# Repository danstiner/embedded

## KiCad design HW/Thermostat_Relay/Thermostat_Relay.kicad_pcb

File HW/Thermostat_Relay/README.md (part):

# Thermostat relay board

## 1. Scope

Control board for two 24 VAC HVAC relays that can be driven by ESP32 GPIO pins. Compatible with
any single-stage gas furnace. Heat pumps are out of scope, they require additional relay channels.
Powering the ESP32 is also out of scope.

## 2. Background

Furnaces take mains power and step it down to 24 VAC. This is supplied on the R wire to a thermostat,
which can close the circuit with the W return wire to call for heat. In a modern furnace this is an
input to a digital control board and only draws a few milliamps. In older furnaces this directly
drives a relay coil and can draw an ampere or more of current.

## 3. Requirements

| ID   | Requirement                                                                                 |
| ---- | ------------------------------------------------------------------------------------------- |
| R-1  | Switch two independent circuits, R–W and R–G, each from one 3.3 V GPIO; high = closed       |
| R-2  | A circuit is open when its input is low or floating, or the MCU is off, in reset or booting |
| R-3  | Carry 1 A RMS continuously per circuit at 50 °C, and switch loads as small as 1 mA          |
| R-4  | Withstand 45 V peak (Class 2 transformer limit: 30 V RMS open-circuit, 42.4 V peak)         |
| R-5  | Survive switching off a 1 A inductive load                                                  |
| R-6  | Leak less than 100 µA through an open circuit                                               |
| R-7  | Galvanically isolate the MCU from the 24 VAC side                                           |
| R-8  | Draw no more than 10 mA per closed circuit from the MCU                                     |
| R-9  | Interrupt a short on the field wiring without damage to the wiring                          |
| R-10 | Surface-mount parts that can be reflowed on a hot plate; through-hole connectors            |

Notes
- 1 A is the load current TI's 24 VAC thermostat relay reference design (TIDA-010085) is
  specified for, and more than half of what a 40 VA Class 2 transformer can supply (1.7 A)
- 50 °C is a conservative ambient
- 30 V RMS maximum for thermostat circuits follows from them being Class 2 under UL 5085-3

## 4. Design trades

### 4.1 24 VAC switch

|                          | Relay    | **PhotoMOS** | Driver + FETs | TPSI8830    | TRIAC       |
| ------------------------ | -------- | ------------ | ------------- | ----------- | ----------- |
| Hold current (R-8)       | 70–90 mA | 5–10 mA      | ~5 mA         | ~5 mA       | ~10 mA      |
| 1 mA load (R-3)          | marginal | ✓            | ✓             | ✓           | ✗           |
| Leakage (R-6)            | ✓        | ✓            | ✓             | ✓           | ✗ (snubber) |
| Parts per channel        | 4        | 4            | ~10           | 3–4         | 5+          |
| Available to buy         | ✓        | ✓            | ✓             | ✗ (preview) | ✓           |
| Short-circuit protection | rugged   | none         | possible      | built in    | none        |

**Chosen: PhotoMOS.** An LED inside the package lights a photovoltaic cell that turns on two
back-to-back MOSFETs. It meets every requirement with only four parts per channel, making it easy
to use for bringing up a v1 board. A separate fuse is added for short-circuit protection.
Downsides of PhotoMOS are slightly higher cost and LED aging.

TI's reference designs for 24 VAC thermostat switching (section 10) both use discrete MOSFET pairs
with a separate isolated gate drive. This is likely a lower cost design at scale production,
using either small transformers or capacitive isolation instead of optocouplers. It also enables
microsecond switching for power-stealing, adding current-sensing circuitry, and the ability
to share one isolated supply across all channels. None of these are relevant to a v1 prototype.

TI's upcoming TPSI8830 is worth watching: it integrates a capacitively isolated driver with
back-to-back MOSFETs and overcurrent protection into a single package with 30 mΩ on resistance.

## 5. Circuit

Two identical channels share the R input, each with its own fuse. Only one channel is shown.

```
 logic side (3.3 V, USB ground) :        furnace side (24 VAC, floating)
                                :
 W_EN    o--+--[R1 220Ω]---+    :    +------+---[F1 2A]--- o R
            |            1 | U1 :    | 6    |
         [R2 10k]        [LED]~~:~~[FETs]  [D1 TVS]
            |            2 |    :    | 4    |
 GND     o--+--------------+    :    +------+------------- o W
```

### 5.1 Switch: Toshiba TLP3109A (U1)

| Datasheet value                 |                               | Requirement     |
| ------------------------------- | ----------------------------- | --------------- |
| Off-state voltage               | 100 V max                     | 45 V peak (R-4) |
| On-state current, AC connection | 3 A at 25 °C, 2.25 A at 50 °C | 1 A (R-3)       |
| On-resistance                   | 50 mΩ typ, 65 mΩ max          | –               |
| LED trigger current             | 3 mA max                      | see 5.2         |
| Off-state leakage, capacitance  | 1 µA max, 460 pF              | see 5.7         |
| Isolation                       | 1500 V RMS                    | galvanic (R-7)  |
| Pulse current                   | 9 A for 100 ms                | see 5.6         |

- Pins 4 and 6 (the two drains) are the switch; pin 5 (common source) is left open. That
  puts the two MOSFETs in series back to back, which is what lets the part block and
  conduct both polarities of AC.
- Heat: at 1 A and the maximum 65 mΩ the switch generates about 0.07 W of heat
- 100 V off-state max was chosen to have margin to clamp surges over the expected 42.4 V peak
  Class 2 transformer output, similar to TI reference design TIDA-010085.

Parts considered (DigiKey, 2026-11-12, quantity 1):

| Part         | Rating       | At 50 °C | R_on max | Isolation | Price           | Outcome     |
| ------------ | ------------ | -------- | -------- | --------- | --------------- | ----------- |
| **TLP3109A** | 100 V, 3 A   | 2.25 A   | 65 mΩ    | 1500 V    | $4.14, in stock | chosen      |
| TLP3546A     | 100 V, 3.5 A | 2.6 A    | 80 mΩ    | 2500 V    | $4.11, no stock | unavailable |

### 5.2 LED resistor: 220 Ω (R1)

The TLP3109A datasheet recommends 5 to 25 mA. `I = (V_GPIO − V_LED) / R`:

| Case            | V_GPIO | V_LED  | I      |
| --------------- | ------ | ------ | ------ |
| Worst-case low  | 3.0 V  | 1.80 V | 5.4 mA |
| Nominal         | 3.3 V  | 1.65 V | 7.5 mA |
| Worst-case high | 3.47 V | 1.50 V | 9.0 mA |

### 5.3 Optional pull-down: 10 kΩ (R2)

Optional pull-down to hold the LED input at ~0 V when not being driven (R-2). Overrides the
pull-up glitch during boot that some ESP32 pins exhibit. Optional because the TLP3109A is
guaranteed off below 0.1 mA of LED current, and a 45 kΩ pull-up supplies only about 0.05 mA.
Cannot override a pin that actively drives high during boot, those high-level glitch pins
should be avoided.

### 5.4 Optional indicator: 4.7 kΩ and a red LED

One LED per channel, from the control input to ground, lit while the ESP32 commands the
channel closed. At 4.7 kΩ it draws about 0.3 mA, 0.4 mA worst case. With the pull-down and
indicator both fitted, a closed channel draws at most 9.0 + 0.35 + 0.4 = 9.7 mA (R-8).

### 5.5 Clamp: Bidirectional TVS (D1)

When the switch opens on a relay coil or gas valve, the coil's inductance creates a voltage
spike across the switch. A bidirectional TVS across the switch limits that voltage (R-5)
to prevent damage to the switch.

|                     | SMBJ48CA       | Requirement                       |
| ------------------- | -------------- | --------------------------------- |
| Reverse stand off   | 48 V           | ≥ 45 V peak (R-4)                 |
| Max clamp           | 77.4 V @ 7.8 A | ≤ 80 V (switch's recommended max) |
| Max reverse leakage | 1 µA           | < 100 µA total leakage (R-6)      |

An RC snubber is ruled out by R-6: a typical 100 nF passes about 1.1 mA at 60 Hz with the
switch open, which could trigger a phantom call for heat on a modern furnace control board.

### 5.6 Fuses: 2 A very fast-acting, one per channel (F1, F2)

Each fuse opens if its W or G circuit is shorted while that channel is closed (R-9): a
shorted relay coil, or the wire touching the transformer's return or grounded metal. That
protects the cable, the transformer and, for moderate fault currents, the switch. One fuse
per channel means a fault on the fan wire cannot take out the heat, and each fuse is sized
for one load, not the sum.

| Littelfuse 0466002.NR | Datasheet                            | Requirement                                                         |
| --------------------- | ------------------------------------ | ------------------------------------------------------------------- |
| Voltage rating        | 63 VAC                               | 30 V RMS (R-4)                                                      |
| Interrupting rating   | 50 A at 63 VAC                       | transformer short-circuit current: unmeasured, estimated 10 to 20 A |
| Continuous current    | 1.5 A at 25 °C, about 1.3 A at 50 °C | 1 A (R-3)                                                           |
| Opens at 200 % (4 A)  | within 5 s                           | –                                                                   |
| Opens at 300 % (6 A)  | within 0.2 s                         | –                                                                   |
| Melting I²t           | 0.23 A²s                             | below the switch's 8 A²s                                            |
| Cold resistance       | 30 mΩ                                | –                                                                   |

- Sizing: Littelfuse's guidance is to run a fuse at no more than 75 % of its rating at
  25 °C, which gives 1.5 A. The datasheet rerates a further 20 % at 70 °C; interpolating,
  about 11 % at 50 °C gives 1.3 A. That leaves about 30 % margin over a 1 A load. Relay
  coil inrush against the low melting I²t is unverified (section 9).
- Compared with others: TI recommends the same 2 A fast fuse for its 1 A design
  (TIDA-010085) and tested with the 1.5 A part of this series. Furnace control boards
  commonly fuse the whole 24 V circuit at 3 or 5 A, so a 2 A fuse here should open first.
- Overloads: the fuse's 2 A rating is below the switch's 2.25 A rating at 50 °C. It holds
  2 A indefinitely and opens slowly just above that (4 A in 5 s and 6 A in 0.2 s are
  specified), so
  moderate overloads are covered loosely, not tightly.
- Shorts: the switch tolerates 9 A for 100 ms, about 8 A²s. At 9 A the fuse melts in
  roughly 3 ms (0.23 A²s / (9 A)²), so the switch should survive a short the transformer
  limits to 9 A. Above 9 A the switch is outside its rating however fast the fuse clears.
  For scale, TI measured about 7 A peak from a shorted 20 VA transformer in TIDA-010085.

Why not a resettable PTC:

|                                      | Fuse, 2 A (chosen) | PTC, e.g. 2920L110/60 (1.1 A hold) |
| ------------------------------------ | ------------------ | ---------------------------------- |
| Carries 1 A at 50 °C                 | yes                | no: hold current falls to 0.83 A   |
| Clears a 9 A short in                | about 3 ms         | about 0.5 s (at 8 A)               |
| Lets through (switch survives 8 A²s) | about 0.2 A²s      | tens of A²s                        |
| After a fault                        | replace the part   | resets itself                      |

A PTC large enough to carry 1 A hot trips more slowly still, so it would protect the
wiring but not the switch. A fuse drawn as a thin PCB trace is not an option: it has no
defined rating and fails by burning the board.

### 5.7 Leakage when open (R-6)

At 30 VAC, 60 Hz: 1 µA (switch) + 5.2 µA (its 460 pF) + 1 µA (TVS) + about 6 µA (TVS
capacitance, about 500 pF read off the datasheet graph) ≈ 13 µA, against a 100 µA limit.

### 5.8 Isolation (R-7)

Isolation is needed because the two sides have unrelated references. The furnace's 24 VAC
secondary is often bonded to chassis earth at C, and the ESP32's USB ground can reach earth
through a PC or charger; a shared connection would tie the two together, and R, W and G
swing up to ±42 V against it, far outside what a GPIO tolerates. A switch for AC also has
to float with the line it switches.

The only link between the two sides is the light path inside U1 and U2, rated 1500 V RMS.
That is far above anything a 24 VAC Class 2 circuit produces, but it is functional
isolation, not a safety rating. The field side is never connected to logic ground; C is a
parking terminal.

### 5.9 PCB layout

| Rule                                 | Value     | Basis                                                        |
| ------------------------------------ | --------- | ------------------------------------------------------------ |
| Field trace width, 1 oz outer layer  | ≥ 0.93 mm | IPC-2152: 10 °C rise at 2 A (fuse rating)                    |
| Spacing between different field nets | ≥ 0.64 mm | IPC-2221C Table 6-1, 51–100 V, bare external conductors (B2) |
| Logic copper to field copper         | ≥ 4.0 mm  | creepage of the 2.54SOP package; no copper under U1 and U2   |

- Trace width: the minimum comes from the Brooks and Adam fit to the IPC-2152 data that
  KiCad's calculator uses, ΔT = 215.3 · I² · W^−1.15 · Th^−1 (W and Th in mils), for a 10
  °C rise at 2 A in 35 µm copper. The older IPC-2221 formula gives 0.78 mm for the same
  conditions. The board uses copper pours at least 1.4 mm wide for the switched nets on
  the front, a pour on the back for R, and 1.0 mm traces with two vias from each fuse to
  that pour. A short does not matter here: the fuse melts in milliseconds.
- Field spacing: the working voltage is at most 42.4 V peak (R-4), but the clamp lets a
  turn-off transient reach 77 V (5.5), so the 51–100 V row applies. It asks for 0.64 mm
  between bare conductors, 0.5 mm between uncoated component leads and 0.3 mm under solder
  mask. Using 0.64 mm everywhere covers all three.
- Logic to field: no standard sets a distance for functional isolation of a Class 2
  circuit, so the relay package is the limit. The TLP3109A datasheet does not state its
  creepage; Toshiba's 2014 photocoupler catalog lists 4.0 mm minimum creepage and
  clearance for the 2.54SOP4/6/8 package family. The footprint's input and output pads are
  5.1 mm apart, and the layout keeps at least 4.9 mm between all logic and field copper,
  including the ground pours on both layers of the logic side.

## 6. Bill of materials

| Ref    | Value              | Part               | Footprint   | Description                                   |
| ------ | ------------------ | ------------------ | ----------- | --------------------------------------------- |
| U1, U2 | TLP3109A           | Toshiba            | 2.54SOP6    | PhotoMOS relay, 100 V, 1 A at 50 °C (5.1)     |
| R1, R3 | 220 Ω, 1 %         | any                | 0603        | RES - Input current limit (5.2)               |
| R2, R4 | 10 kΩ              | any                | 0603        | Input pull-down, optional (5.3)               |
| D1, D2 | 48 V               | SMBJ48CA           | SMB         | Bidirectional TVS, 48 V standoff (5.5)        |
| F1, F2 | 2 A very fast      | Littelfuse 0466002 | 1206        | Fuse, ≥ 30 VAC, ≥ 20 A interrupting (5.6)     |
| R5, R6 | 4.7 kΩ             | any                | 0603        | RES - Indicator current limit, optional (5.4) |
| D3, D4 | Red LED            | any                | 0603        | LED, Red, SMD - Indicator, optional (5.4)     |
| J1     | 1×3 pin header     | any                | 2.54 mm THT | MCU Connection                                |
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
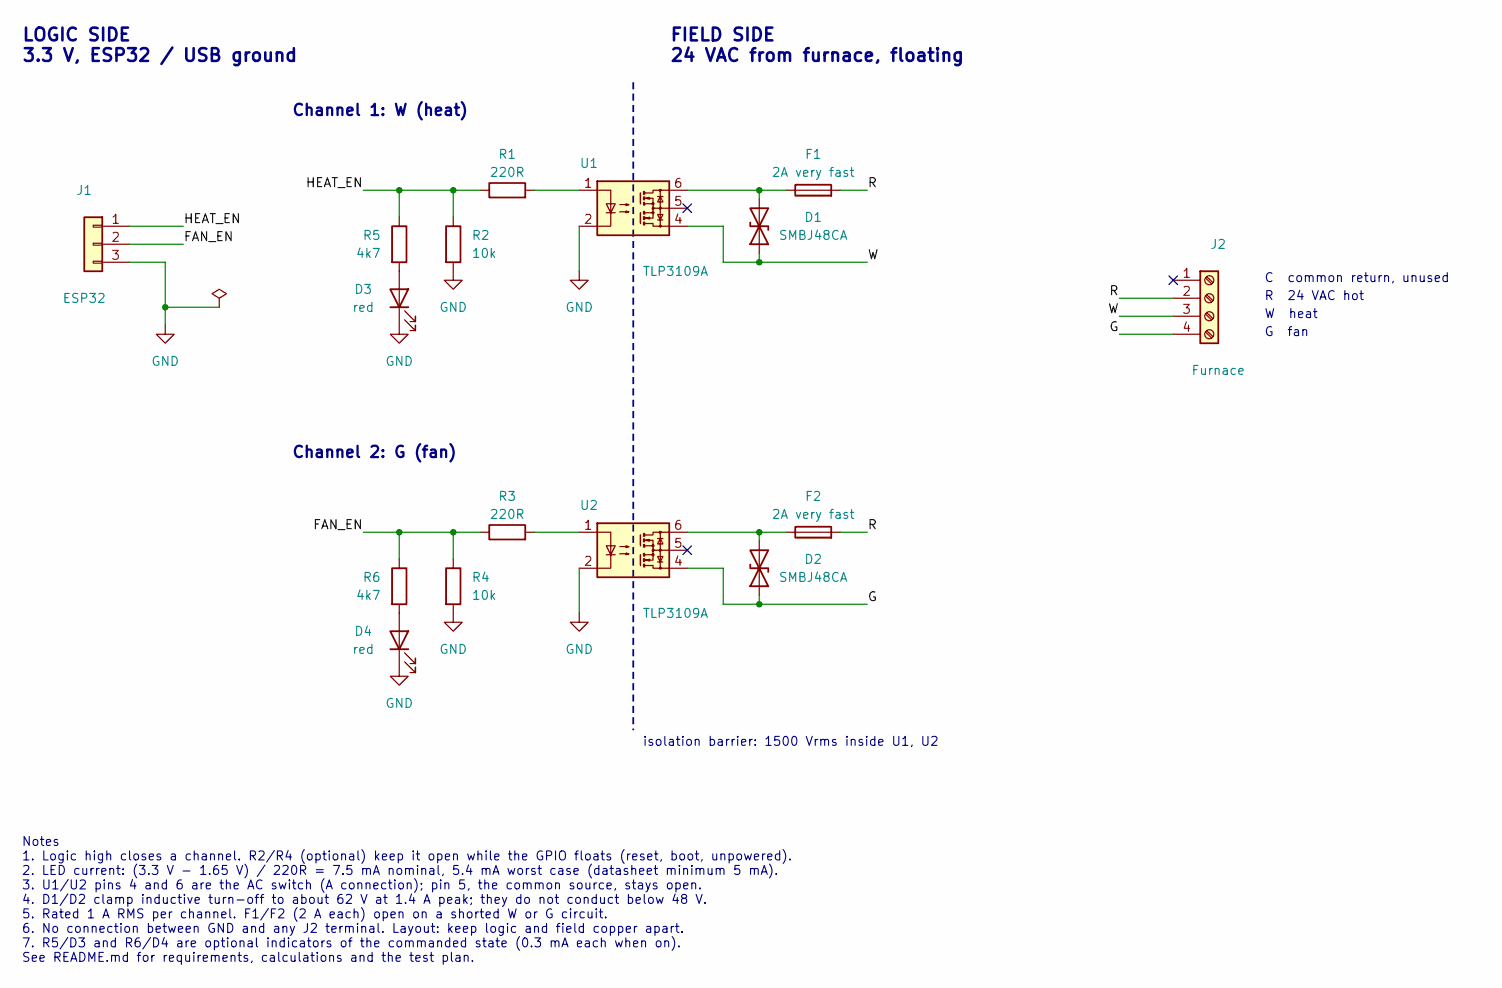
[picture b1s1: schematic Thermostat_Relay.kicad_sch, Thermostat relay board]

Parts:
D1, D2: SMBJ48CA; D_SMB_Handsoldering; MPN SMBJ48CA
D3, D4: red; LED_0603_1608Metric_Pad1.05x0.95mm_HandSolder; MPN 150060SS75000
F1, F2: 2A very fast; Fuse_1206_3216Metric_Pad1.42x1.75mm_HandSolder; MPN 0466002.NR
J1: ESP32; PinHeader_1x03_P2.54mm_Vertical
J2: Furnace; TerminalBlock_Phoenix_MKDS-1,5-4-5.08_1x04_P5.08mm_Horizont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
R1, R3: 220R; R_0603_1608Metric_Pad0.98x0.95mm_HandSolder; Tolerance 1%; MPN RC0603FR-07220RL
R2, R4: 10k; R_0603_1608Metric_Pad0.98x0.95mm_HandSolder; MPN RC0603FR-0710KL
R5, R6: 4k7; R_0603_1608Metric_Pad0.98x0.95mm_HandSolder; MPN RC0603FR-074K7L
U1, U2: TLP3109A; Toshiba_11-7C1S_2.54SOP6_4.4x6.3mm_P2.54mm; MPN TLP3109A(TP,F

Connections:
/G: D2.1 (A1), J2.4, U2.4
/G_EN: J1.2, R3.1, R4.1, R6.1
/R: F1.2, F2.2, J2.2
/W: D1.1 (A1), J2.3, U1.4
/W_EN: J1.1, R1.1, R2.1, R5.1
GND: D3.1 (K), D4.1 (K), J1.3, R2.2, R4.2, U1.2, U2.2
unnamed: D1.2 (A2), F1.1, U1.6
unnamed: D2.2 (A2), F2.1, U2.6
unnamed: D3.2 (A), R5.2
unnamed: D4.2 (A), R6.2
unnamed: R1.2, U1.1
unnamed: R3.2, U2.1

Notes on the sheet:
FIELD SIDE 24 VAC from furnace, floating
R 24 VAC hot
LOGIC SIDE 3.3 V, ESP32 / USB ground
Channel 2: G (fan)
W heat
Channel 1: W (heat)
Notes 1. Logic high closes a channel. R2/R4 (optional) keep it open while the GPIO floats (reset, boot, unpowered). 2. LED current: (3.3 V - 1.65 V) / 220R = 7.5 mA nominal, 5.4 mA worst case (datasheet minimum 5 mA). 3. U1/U2 pins 4 and 6 are the AC switch (A connection); pin 5, the common source,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
G fan
C common return, unused
isolation barrier: 1500 Vrms inside U1, U2

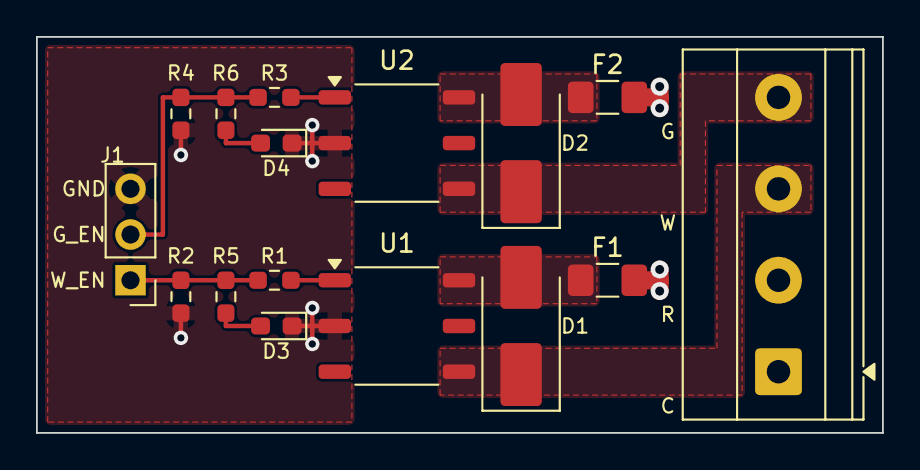
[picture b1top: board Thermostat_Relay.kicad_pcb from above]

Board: 2 copper layers, 47.0 x 22.0 mm, 16 parts (0 on the bottom side), 12 nets.

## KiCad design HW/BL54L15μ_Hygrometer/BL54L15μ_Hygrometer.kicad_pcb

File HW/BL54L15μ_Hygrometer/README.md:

+-----------+-----+----------------------+-----------------------------------------+--------------------------------------------------------------------------------------+
| Reference | Qty | Value                | Part Number                             | Footprint                                                                            |
+-----------+-----+----------------------+-----------------------------------------+--------------------------------------------------------------------------------------+
| BT1       | 1   | CR2 Battery          | 1011                                    | 1011:BAT_1011                                                                        |
| BZ1       | 1   | AST0827MW-03BTRQ     | AST0827MW-03BTRQ                        | AST0827MW-03BTRQ:AST0827MW-03BTRQ_MAL                                                |
| C1        | 1   | 100nF                | GRM155R61A104KA01J                      | Capacitor_SMD:C_0402_1005Metric                                                      |
| C2,C3     | 2   | 10μF                 | CL10A106KP8NNNC                         | Capacitor_SMD:C_0603_1608Metric                                                      |
| D1,D2     | 2   | 5V TVS               | TPD1E10B06DPYR                          | Diode_SMD:D_0402_1005Metric                                                          |
| D3        | 1   | MBR0520L             | MBR0520LT3G                             | Diode_SMD:D_SOD-123                                                                  |
| IC1       | 1   | nrf54L 453-00223R    | 453-00223R                              | 453-00223R:45300223R                                                                 |
| J1        | 1   | Conn_ARM_JTAG_SWD_10 | 3220-10-0300-00                         | Connector_PinHeader_1.27mm:PinHeader_2x05_P1.27mm_Vertical_SMD                       |
| P1,P2     | 2   | 6mmMetalDome         | Triangle 6mm - 0.8mm feet               | MetalDomeSwitch:TriangleDome_Diameter6mm                                             |
| Q1        | 1   | AOSS32136C           | AOSS32136C                              | Package_TO_SOT_SMD:SOT-23-3                                                          |
| R1,R2     | 2   | 10kΩ                 | RC0402FR-0710KL                         | Resistor_SMD:R_0402_1005Metric                                                       |
| R3,R7     | 2   | 1MΩ                  | RC0402FR-071ML                          | Resistor_SMD:R_0402_1005Metric                                                       |
| U1        | 1   | SHT4x                | SHT45-AD1F-R2                           | Sensor_Humidity:Sensirion_DFN-4_1.5x1.5mm_P0.8mm_SHT4x_NoCentralPad                  |
| X1        | 1   | 32.768 kHz           | CM7V-T1A-LOW-ESR-32.768KHZ-9PF-20-TA-QC | CM7V_T1A_LOW_ESR_32_768KHZ_9PF_20_TA_QC:XTAL_CM7V-T1A-LOW-ESR-32.768KHZ-9PF-20-TA-QC |
+-----------+-----+----------------------+-----------------------------------------+--------------------------------------------------------------------------------------+

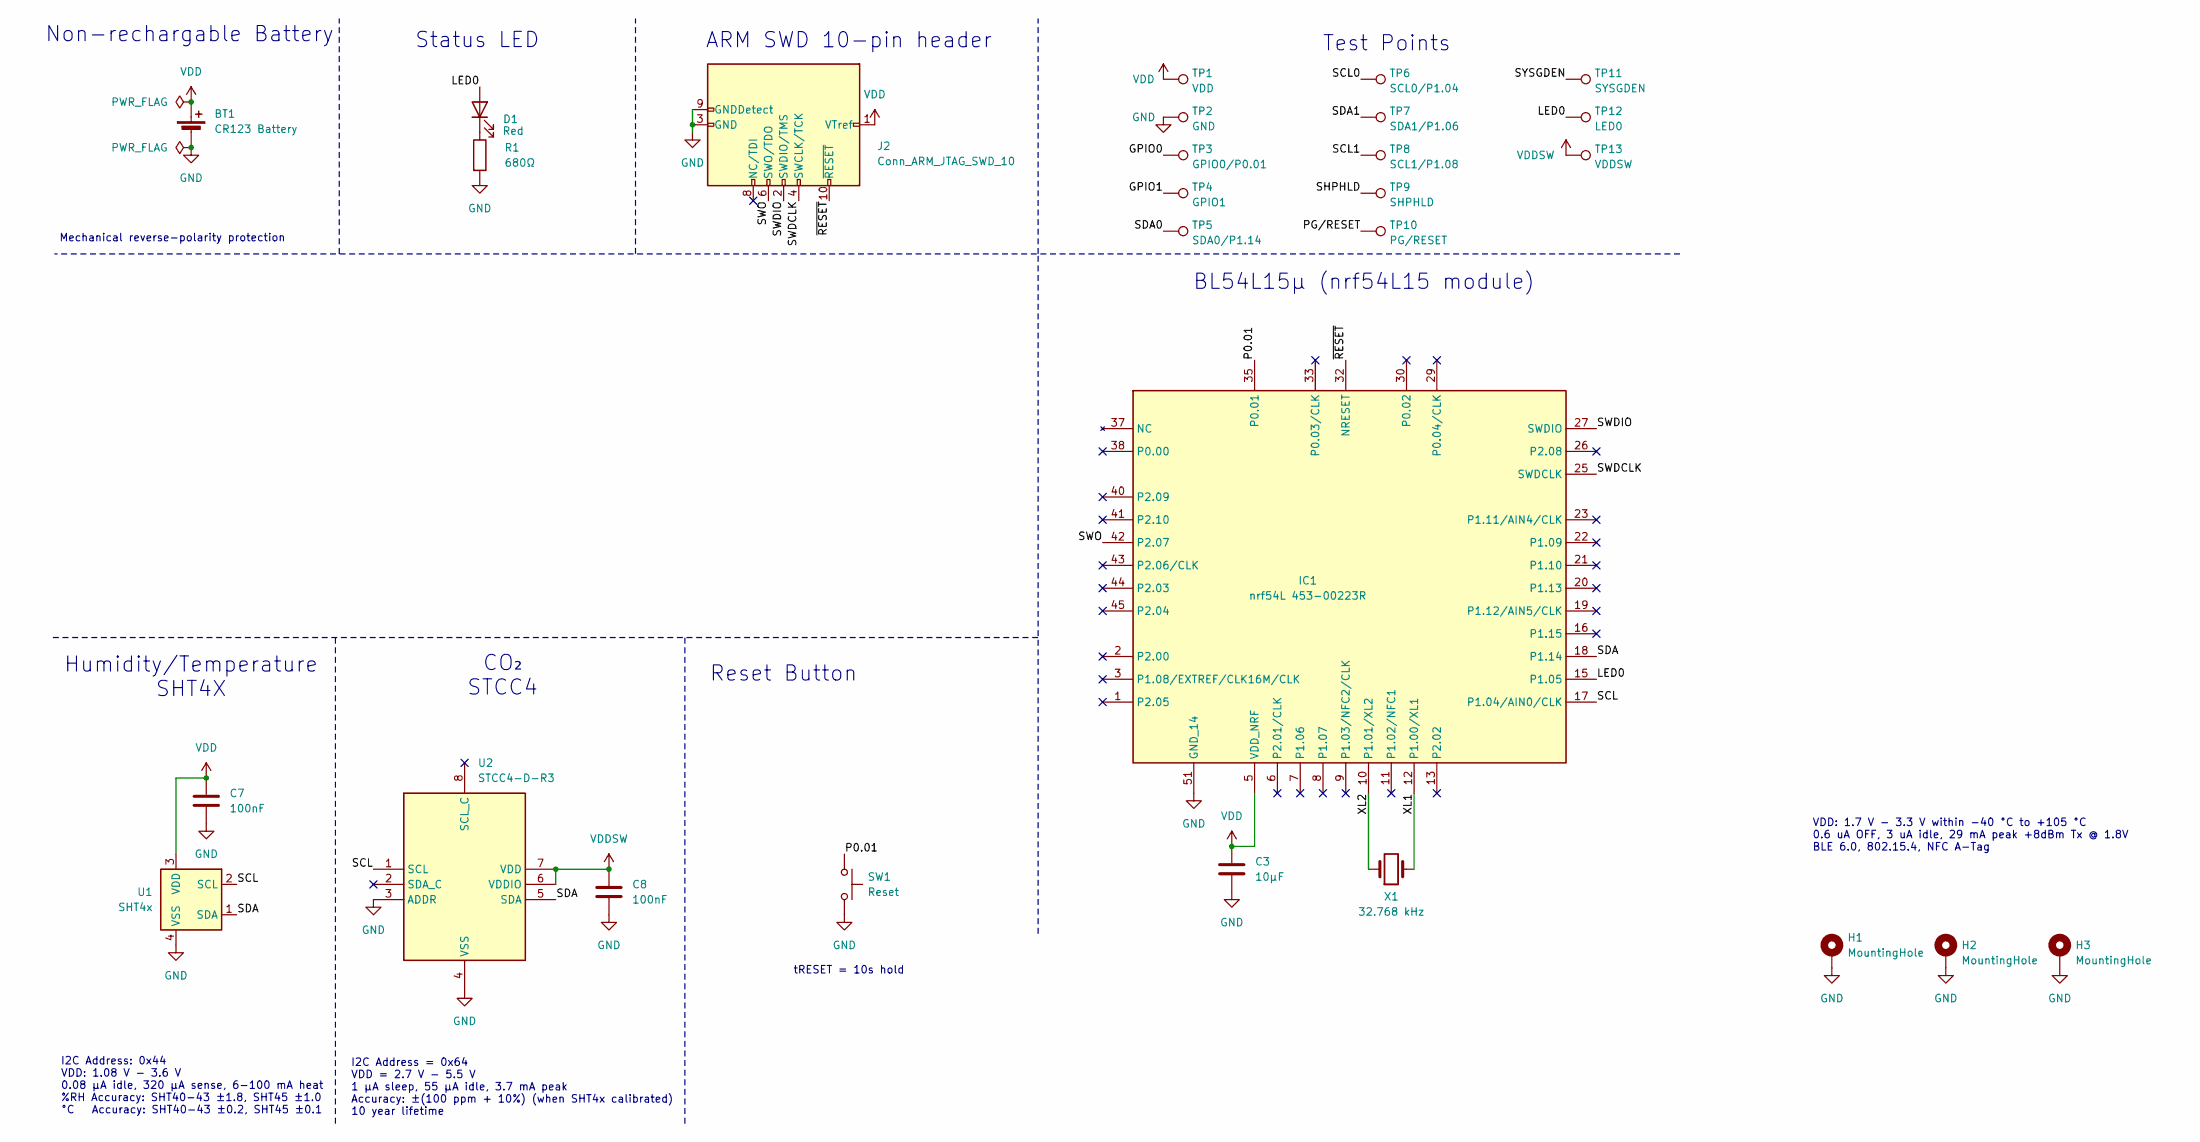
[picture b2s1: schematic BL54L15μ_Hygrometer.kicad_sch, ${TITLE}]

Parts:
BT1: CR123 Battery; BAT_1011; Part Number 1011
C3: 10μF; C_0603_1608Metric; Part Number CL10A106KP8NNNC
C7, C8: 100nF; C_0402_1005Metric; Part Number GRM155R61A104KA01J
D1: PWRLED; LED_0603_1608Metric; Part Number 150060SS75000; Digikey Part Number 732-4979-1-ND
H1, H2, H3: MountingHole; MountingHole_2.2mm_M2_Pad
IC1: nrf54L 453-00223R; 45300223R; Part Number 453-00223R; Digikey Part Number 776-453-00223RCT-ND
J2: Conn_ARM_JTAG_SWD_10; PinHeader_2x05_P1.27mm_Vertical_SMD; Digikey Part Number 1528-752-ND
R1: 680Ω; R_0603_1608Metric; Part Number RC0603JR-13680RL
SW1: Reset; SW_Push_SPST_NO_Alps_SKRK; Part Number SKRKAHE020; Digikey Part Number 4809-SKRKAHE020CT-ND
TP1: VDD; TestPoint_Pad_D1.0mm
TP2: GND; TestPoint_Pad_1.0x1.0mm
TP3: GPIO0/P0.01; TestPoint_Pad_D1.0mm
TP4: GPIO1; TestPoint_Pad_D1.0mm
TP5: SDA0/P1.14; TestPoint_Pad_D1.0mm
TP6: SCL0/P1.04; TestPoint_Pad_D1.0mm
TP7: SDA1/P1.06; TestPoint_Pad_D1.0mm
TP8: SCL1/P1.08; TestPoint_Pad_D1.0mm
TP9: SHPHLD; TestPoint_Pad_D1.0mm
TP10: PG/RESET; TestPoint_Pad_D1.0mm
TP11: SYSGDEN; TestPoint_Pad_D1.0mm
TP12: LED0; TestPoint_Pad_D1.0mm
TP13: VDDSW; TestPoint_Pad_D1.0mm
U1: SHT4x; Sensirion_DFN-4_1.5x1.5mm_P0.8mm_SHT4x_NoCentralPad; Part Number SHT45-AD1F-R2
U2: STCC4-D-R3; STCC4DR3; Part Number STCC4-D-R3; Digikey Part Number 1649-STCC4-D-R3CT-ND
X1: 32.768 kHz; XTAL_CM7V-T1A-LOW-ESR-32.768KHZ-9PF-20-TA-QC; Part Number CM7V-T1A-LOW-ESR-32.768KHZ-9PF-20-TA-QC; Digikey Part Number 2195-CM7VT1ALOWESR32.768KHZ9PF20TAQCCT-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

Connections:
/GPIO0: TP3.1 (1_1)
/GPIO1: TP4.1 (1_1)
/LED0: D1.2 (A), IC1.15 (P1.05), TP12.1 (1_1)
/P0.01: IC1.35 (P0.01), SW1.1
/PG/RESET: TP10.1 (1_1)
/SCL: IC1.17 (P1.04/AIN0/CLK), U1.2 (SCL), U2.1 (SCL)
/SCL0: TP6.1 (1_1)
/SCL1: TP8.1 (1_1)
/SDA: IC1.18 (P1.14), U1.1 (SDA), U2.5 (SDA)
/SDA0: TP5.1 (1_1)
/SDA1: TP7.1 (1_1)
/SHPHLD: TP9.1 (1_1)
/SWDCLK: IC1.25 (SWDCLK), J2.4 (SWCLK/TCK)
/SWDIO: IC1.27 (SWDIO), J2.2 (SWDIO/TMS)
/SWO: IC1.42 (P2.07), J2.6 (SWO/TDO)
/SYSGDEN: TP11.1 (1_1)
/XL1: IC1.12 (P1.00/XL1), X1.2
/XL2: IC1.10 (P1.01/XL2), X1.1
/~RESET: IC1.32 (NRESET), J2.10 (~RESET)
GND: BT1.2 (-), C3.2, C7.2, C8.2, H1.1 (1_1), H2.1 (1_1), H3.1 (1_1), IC1.4 (GND_1), IC1.14 (GND_2), IC1.24 (GND_3), IC1.28 (GND_4), IC1.31 (GND_5), IC1.34 (GND_6), IC1.36 (GND_7), IC1.39 (GND_8), IC1.46 (GND_9), IC1.47 (GND_10), IC1.48 (GND_11), IC1.49 (GND_12), IC1.50 (GND_13), IC1.51 (GND_14), J2.3 (GND), J2.5 (GND), J2.9 (GNDDetect), R1.2, SW1.2, TP2.1 (1_1), U1.4 (VSS), U2.3 (ADDR), U2.4 (VSS)
unnamed: D1.1 (K), R1.1
VDD: BT1.1 (+), C3.1, C7.1, IC1.5 (VDD_NRF), J2.1 (VTref), TP1.1 (1_1), U1.3 (VDD)
VDDSW: C8.1, TP13.1 (1_1), U2.6 (VDDIO), U2.7 (VDD)

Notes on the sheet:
Mechanical reverse-polarity protection
VDD: 1.7 V - 3.3 V within -40 °C to +105 °C 0.6 uA OFF, 3 uA idle, 29 mA peak +8dBm Tx @ 1.8V BLE 6.0, 802.15.4, NFC A-Tag
Humidity/Temperature SHT4X
CO₂ STCC4
tRESET = 10s hold
I2C Address = 0x64 VDD = 2.7 V - 5.5 V 1 μA sleep, 55 μA idle, 3.7 mA peak Accuracy: ±(100 ppm + 10%) (when SHT4x calibrated) 10 year lifetime
Test Points
Non-rechargable Battery
BL54L15μ (nrf54L15 module)
Status LED
I2C Address: 0x44 VDD: 1.08 V - 3.6 V 0.08 μA idle, 320 μA sense, 6-100 mA heat %RH Accuracy: SHT40-43 ±1.8, SHT45 ±1.0 °C Accuracy: SHT40-43 ±0.2, SHT45 ±0.1
ARM SWD 10-pin header
Reset Button

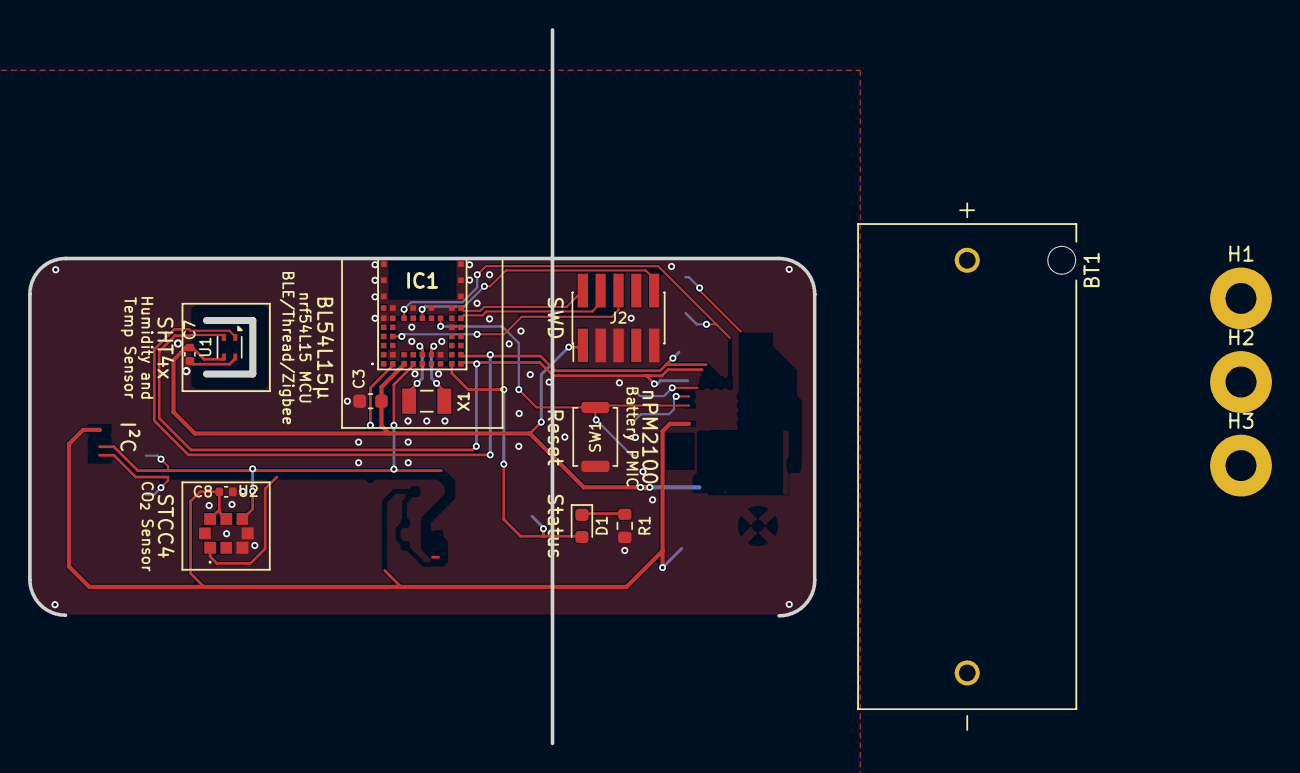
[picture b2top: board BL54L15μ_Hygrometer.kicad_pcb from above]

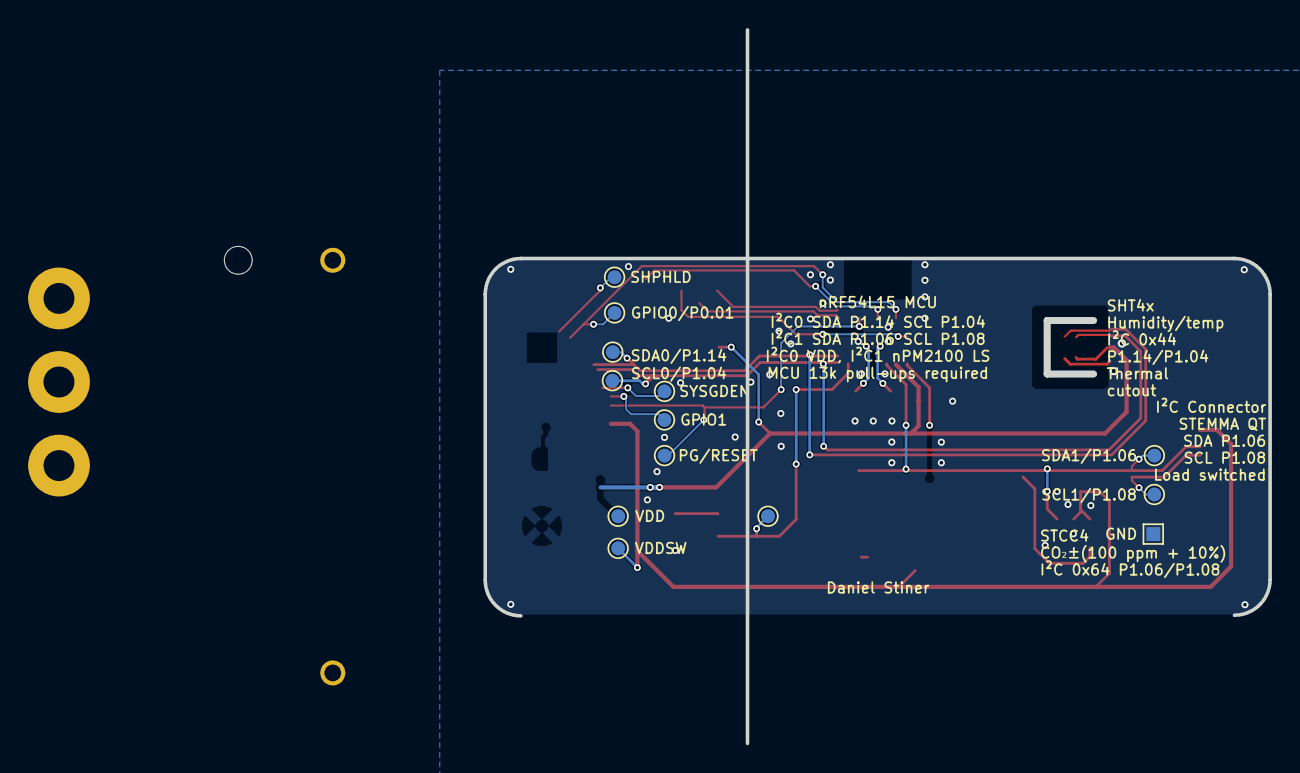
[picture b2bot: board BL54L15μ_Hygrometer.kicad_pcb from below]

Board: 2 copper layers, 55.9 x 50.8 mm, 28 parts (13 on the bottom side), 14 nets.

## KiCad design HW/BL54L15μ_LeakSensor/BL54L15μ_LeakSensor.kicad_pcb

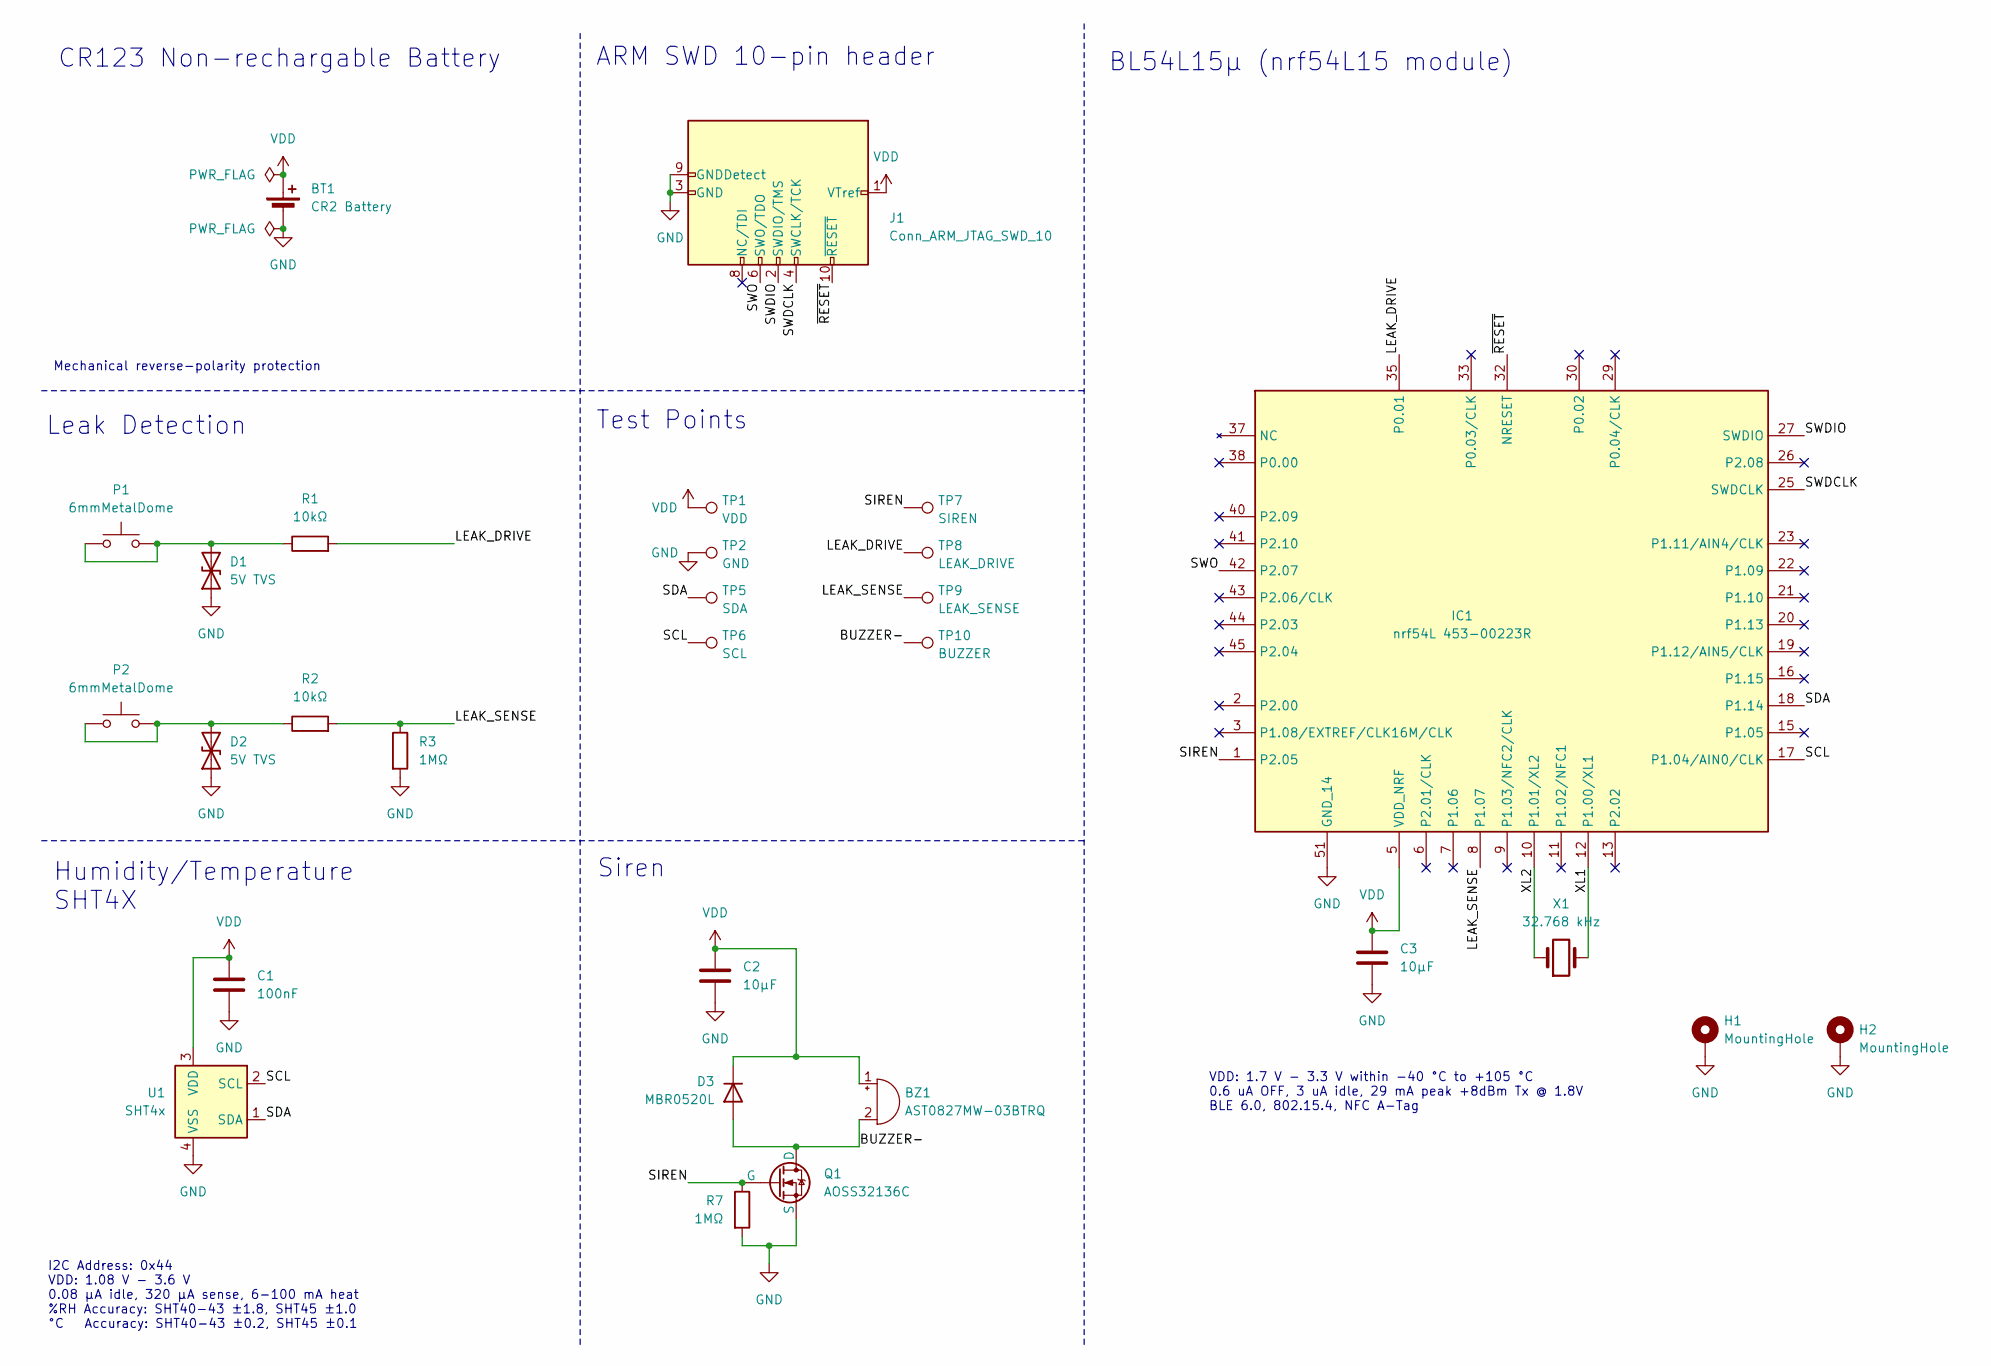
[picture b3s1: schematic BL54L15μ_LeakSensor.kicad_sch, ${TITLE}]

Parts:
BT1: CR2 Battery; BAT_1011; Part Number 1011
BZ1: AST0827MW-03BTRQ; AST0827MW-03BTRQ_MAL; Part Number AST0827MW-03BTRQ
C1: 100nF; C_0402_1005Metric; Part Number GRM155R61A104KA01J
C2, C3: 10μF; C_0603_1608Metric; Part Number CL10A106KP8NNNC
D1, D2: 5V TVS; D_0402_1005Metric; Part Number TPD1E10B06DPYR
D3: MBR0520L; D_SOD-123; Part Number MBR0520LT3G
H1, H2: MountingHole; MountingHole_2.2mm_M2_Pad
IC1: nrf54L 453-00223R; 45300223R; Part Number 453-00223R; Digikey Part Number 776-453-00223RCT-ND
J1: Conn_ARM_JTAG_SWD_10; PinHeader_2x05_P1.27mm_Vertical_SMD; Part Number 3220-10-0300-00
P1, P2: 6mmMetalDome; TriangleDome_Diameter6mm; Part Number Triangle 6mm - 0.8mm feet
Q1: AOSS32136C; SOT-23-3; Part Number AOSS32136C
R1, R2: 10kΩ; R_0402_1005Metric; Part Number RC0402FR-0710KL
R3, R7: 1MΩ; R_0402_1005Metric; Part Number RC0402FR-071ML
TP1: VDD; TestPoint_Pad_D1.0mm
TP2: GND; TestPoint_Pad_1.0x1.0mm
TP5: SDA; TestPoint_Pad_D1.0mm
TP6: SCL; TestPoint_Pad_D1.0mm
TP7: SIREN; TestPoint_Pad_D1.0mm
TP8: LEAK_DRIVE; TestPoint_Pad_D1.0mm
TP9: LEAK_SENSE; TestPoint_Pad_D1.0mm
TP10: BUZZER; TestPoint_Pad_D1.0mm
U1: SHT4x; Sensirion_DFN-4_1.5x1.5mm_P0.8mm_SHT4x_NoCentralPad; Part Number SHT45-AD1F-R2
X1: 32.768 kHz; XTAL_CM7V-T1A-LOW-ESR-32.768KHZ-9PF-20-TA-QC; Part Number CM7V-T1A-LOW-ESR-32.768KHZ-9PF-20-TA-QC; Digikey Part Number 2195-CM7VT1ALOWESR32.768KHZ9PF20TAQCCT-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

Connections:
/BUZZER: BZ1.2 (-), D3.2 (A), Q1.1 (D), TP10.1 (1_1)
/LEAK_DRIVE: IC1.35 (P0.01), R1.2, TP8.1 (1_1)
/LEAK_SENSE: IC1.8 (P1.07), R2.2, R3.1, TP9.1 (1_1)
/SCL: IC1.17 (P1.04/AIN0/CLK), TP6.1 (1_1), U1.2 (SCL)
/SDA: IC1.18 (P1.14), TP5.1 (1_1), U1.1 (SDA)
/SIREN: IC1.1 (P2.05), Q1.2 (G), R7.1, TP7.1 (1_1)
/SWDCLK: IC1.25 (SWDCLK), J1.4 (SWCLK/TCK)
/SWDIO: IC1.27 (SWDIO), J1.2 (SWDIO/TMS)
/SWO: IC1.42 (P2.07), J1.6 (SWO/TDO)
/XL1: IC1.12 (P1.00/XL1), X1.2
/XL2: IC1.10 (P1.01/XL2), X1.1
/~RESET: IC1.32 (NRESET), J1.10 (~RESET)
GND: BT1.2 (-), C1.2, C2.2, C3.2, D1.1 (A1), D2.1 (A1), H1.1 (1_1), H2.1 (1_1), IC1.4 (GND_1), IC1.14 (GND_2), IC1.24 (GND_3), IC1.28 (GND_4), IC1.31 (GND_5), IC1.34 (GND_6), IC1.36 (GND_7), IC1.39 (GND_8), IC1.46 (GND_9), IC1.47 (GND_10), IC1.48 (GND_11), IC1.49 (GND_12), IC1.50 (GND_13), IC1.51 (GND_14), J1.3 (GND), J1.5 (GND), J1.9 (GNDDetect), Q1.3 (S), R3.2, R7.2, TP2.1 (1_1), U1.4 (VSS)
unnamed: D1.2 (A2), P1.1, P1.2, R1.1
unnamed: D2.2 (A2), P2.1, P2.2, R2.1
VDD: BT1.1 (+), BZ1.1 (+), C1.1, C2.1, C3.1, D3.1 (K), IC1.5 (VDD_NRF), J1.1 (VTref), TP1.1 (1_1), U1.3 (VDD)

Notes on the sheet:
VDD: 1.7 V - 3.3 V within -40 °C to +105 °C 0.6 uA OFF, 3 uA idle, 29 mA peak +8dBm Tx @ 1.8V BLE 6.0, 802.15.4, NFC A-Tag
CR123 Non-rechargable Battery
Humidity/Temperature SHT4X
Mechanical reverse-polarity protection
Leak Detection
Test Points
BL54L15μ (nrf54L15 module)
I2C Address: 0x44 VDD: 1.08 V - 3.6 V 0.08 μA idle, 320 μA sense, 6-100 mA heat %RH Accuracy: SHT40-43 ±1.8, SHT45 ±1.0 °C Accuracy: SHT40-43 ±0.2, SHT45 ±0.1
ARM SWD 10-pin header
Siren

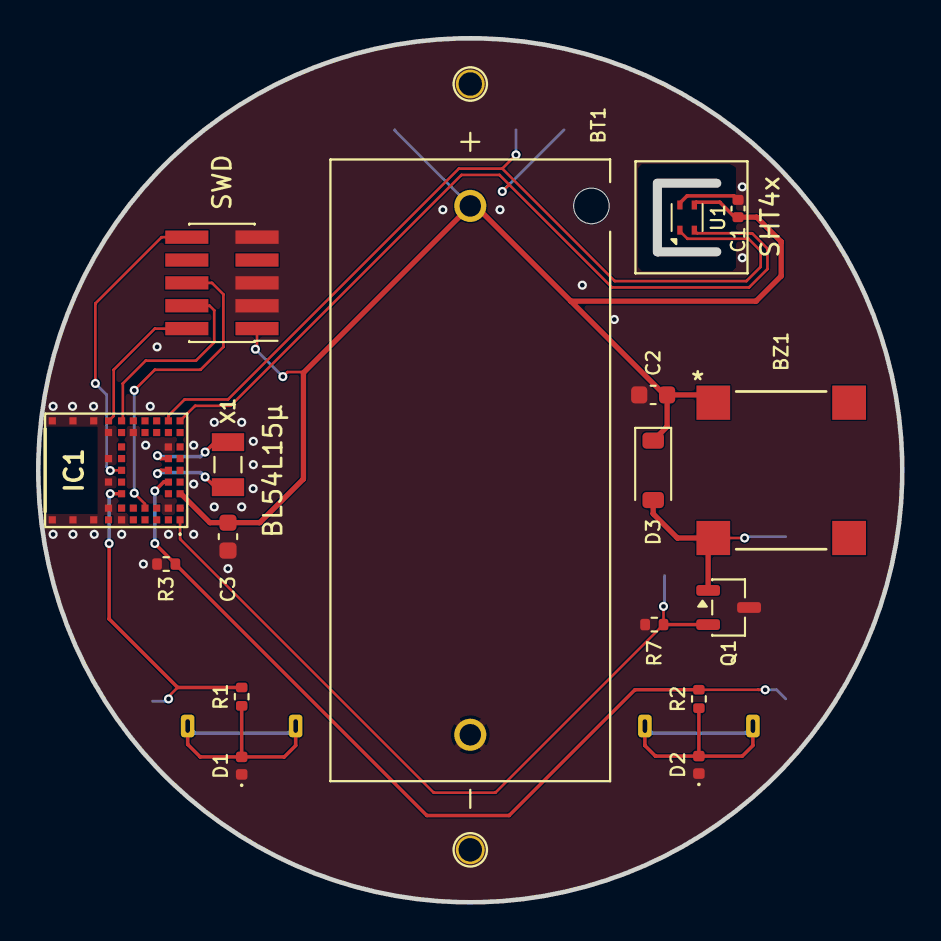
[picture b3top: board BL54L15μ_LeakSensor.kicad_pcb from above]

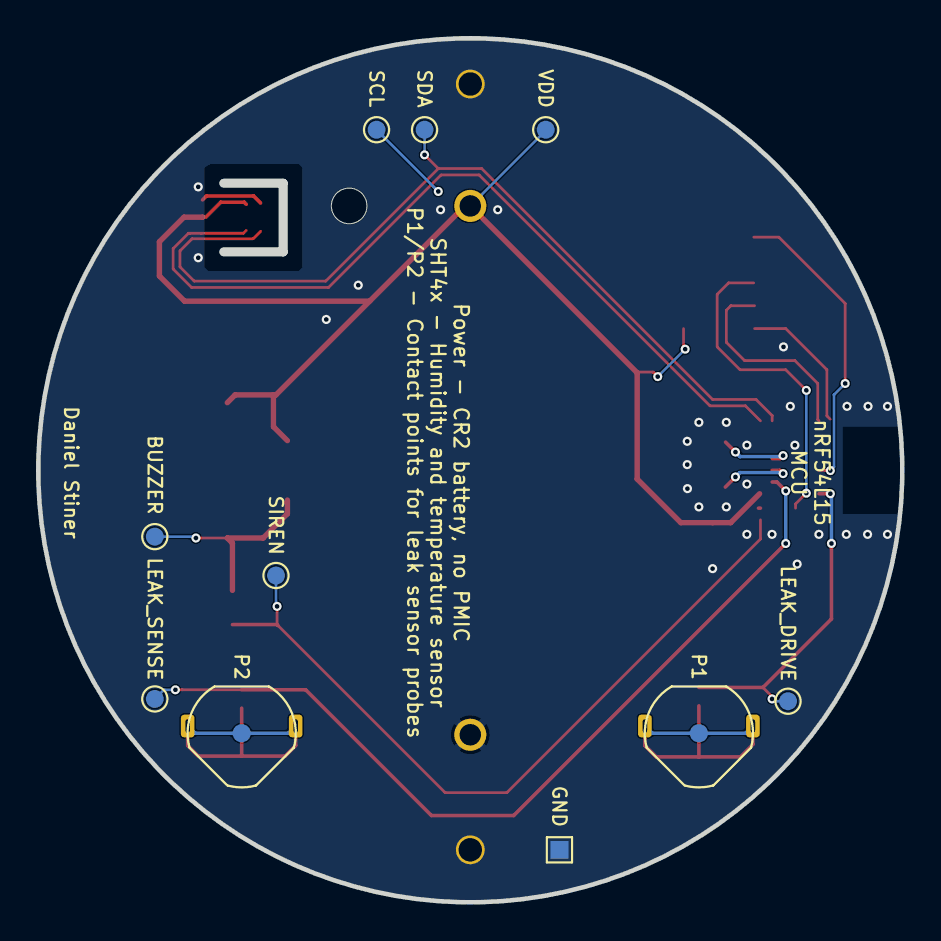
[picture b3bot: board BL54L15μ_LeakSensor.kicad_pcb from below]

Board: 2 copper layers, 48.0 x 48.0 mm, 29 parts (10 on the bottom side), 16 nets.

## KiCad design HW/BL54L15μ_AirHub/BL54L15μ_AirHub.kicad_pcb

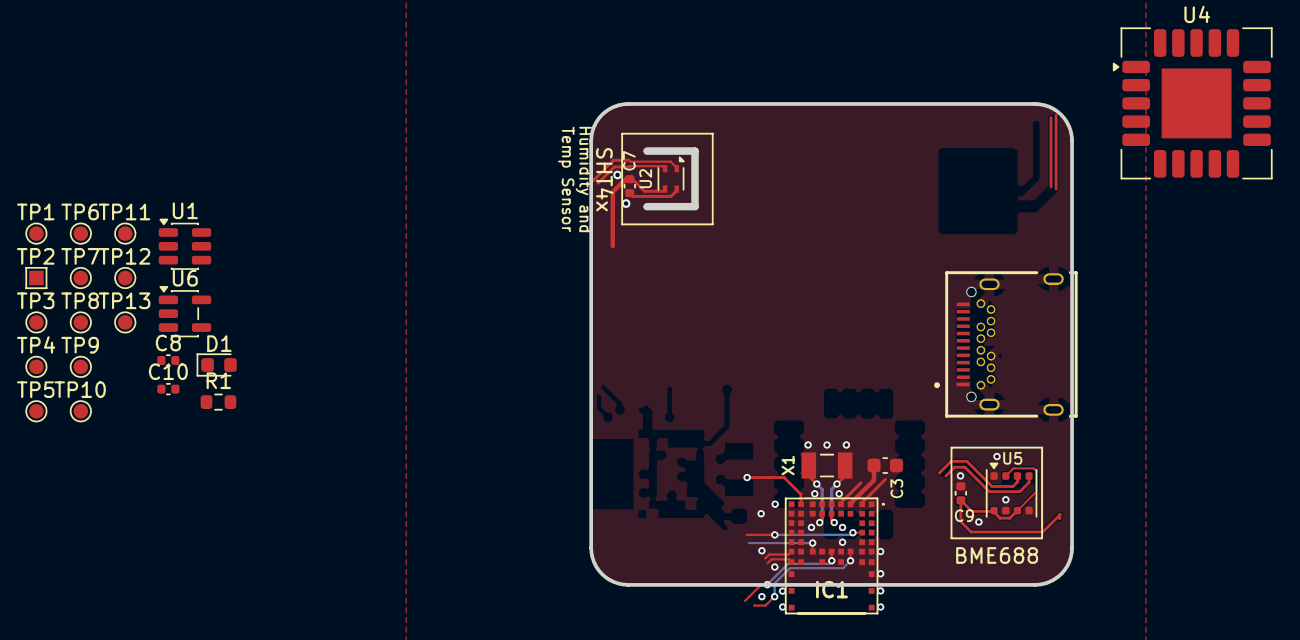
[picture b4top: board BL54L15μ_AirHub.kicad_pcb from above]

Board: 2 copper layers, 33.0 x 33.0 mm, 28 parts (0 on the bottom side), 20 nets.

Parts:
C3: 10μF; C_0603_1608Metric
C7, C8, C9, C10: 100nF; C_0402_1005Metric
D1: PWRLED; LED_0603_1608Metric
IC1: nrf54L 453-00223R; 45300223R
J3: USB_C_Receptacle; GCT_USB4056-03-A_REVA2
R1: 100Ω; R_0603_1608Metric
TP1: VDD; TestPoint_Pad_D1.0mm
TP2: GND; TestPoint_Pad_1.0x1.0mm
TP3: GPIO0/P0.01; TestPoint_Pad_D1.0mm
TP4: GPIO1; TestPoint_Pad_D1.0mm
TP5: SDA0/P1.14; TestPoint_Pad_D1.0mm
TP6: SCL0/P1.04; TestPoint_Pad_D1.0mm
TP7: SDA1/P1.06; TestPoint_Pad_D1.0mm
TP8: SCL1/P1.08; TestPoint_Pad_D1.0mm
TP9: SHPHLD; TestPoint_Pad_D1.0mm
TP10: PG/RESET; TestPoint_Pad_D1.0mm
TP11: SYSGDEN; TestPoint_Pad_D1.0mm
TP12: LED0; TestPoint_Pad_D1.0mm
TP13: VDDSW; TestPoint_Pad_D1.0mm
U1: USBLC6-2SC6; SOT-23-6
U2: SHT4x; Sensirion_DFN-4_1.5x1.5mm_P0.8mm_SHT4x_NoCentralPad
U4: SCD4X; Sensirion_SCD4x-1EP_10.1x10.1mm_P1.25mm_EP4.8x4.8mm
U5: BME688; Bosch_LGA-8_3x3mm_P0.8mm_ClockwisePinNumbering
U6: AP2112K-3.3; SOT-23-5
X1: 32.768 kHz; XTAL_CM7V-T1A-LOW-ESR-32.768KHZ-9PF-20-TA-QC

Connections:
/GPIO0: IC1.35 (P0.01), TP3.1 (1_1)
/LED0: D1.2 (A), IC1.15 (P1.05), TP12.1 (1_1)
/PG/RESET: IC1.29 (P0.04/CLK), TP10.1 (1_1)
/SCL: U2.2 (SCL), U4.9 (SCL), U5.4 (SCK)
/SCL0: IC1.17 (P1.04/AIN0/CLK), TP6.1 (1_1)
/SCL1: IC1.3 (P1.08/EXTREF/CLK16M/CLK), TP8.1 (1_1)
/SDA: U2.1 (SDA), U4.10 (SDA), U5.3 (SDI)
/SDA0: IC1.18 (P1.14), TP5.1 (1_1)
/SDA1: IC1.7 (P1.06), TP7.1 (1_1)
/SWDCLK: IC1.25 (SWDCLK), U1.6 (I/O1)
/SWDIO: IC1.27 (SWDIO), U1.4 (I/O2)
/XL1: IC1.12 (P1.00/XL1), X1.2
/XL2: IC1.10 (P1.01/XL2), X1.1
/~RESET: IC1.32 (NRESET), J3.B2 (TX2+)
GND: C3.2, C7.2, C8.2, C9.2, C10.2, IC1.4 (GND_1), IC1.14 (GND_2), IC1.24 (GND_3), IC1.28 (GND_4), IC1.31 (GND_5), IC1.34 (GND_6), IC1.36 (GND_7), IC1.39 (GND_8), IC1.46 (GND_9), IC1.47 (GND_10), IC1.48 (GND_11), IC1.49 (GND_12), IC1.50 (GND_13), IC1.51 (GND_14), J3.A1 (GND), J3.A12 (GND), J3.B1 (GND), J3.B8 (SBU2), J3.B12 (GND), J3.S1 (SHIELD), R1.2, TP2.1 (1_1), U1.2 (GND), U2.4 (VSS), U4.6 (GND), U4.20 (GND), U4.21 (GND), U5.1 (GND), U5.5 (SDO), U5.7 (GND), U6.2 (GND)
unnamed: D1.1 (K), R1.1
unnamed: J3.A2 (TX1+), U1.3 (I/O2)
unnamed: J3.A3 (TX1-), U1.1 (I/O1)
VBUS: J3.A4 (VBUS), J3.A9 (VBUS), J3.B4 (VBUS), J3.B9 (VBUS), U1.5 (VBUS), U6.1 (VIN), U6.3 (EN)
VDD: C3.1, C7.1, C8.1, C9.1, C10.1, IC1.5 (VDD_NRF), J3.A8 (SBU1), TP1.1 (1_1), U2.3 (VDD), U4.7 (VDD), U4.19 (VDD), U5.2 (CSB), U5.6 (VDDIO), U5.8 (VDD), U6.5 (VOUT)
